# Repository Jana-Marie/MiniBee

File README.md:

# MiniBee

STM32WB5 based Zigbee (and other RF protocols) to adressable LED (e.g. WS2812, SK6812) bridge with a footprint of just 22*23.5mm and USB.

<table>
  <tbody>
    <tr>
      <td>
        
      </td>
      <td>
        
      </td>
    </tr>
    <tr>
      <td colspan="2">
        
      </td>
    </tr>
  </tbody>
</table>

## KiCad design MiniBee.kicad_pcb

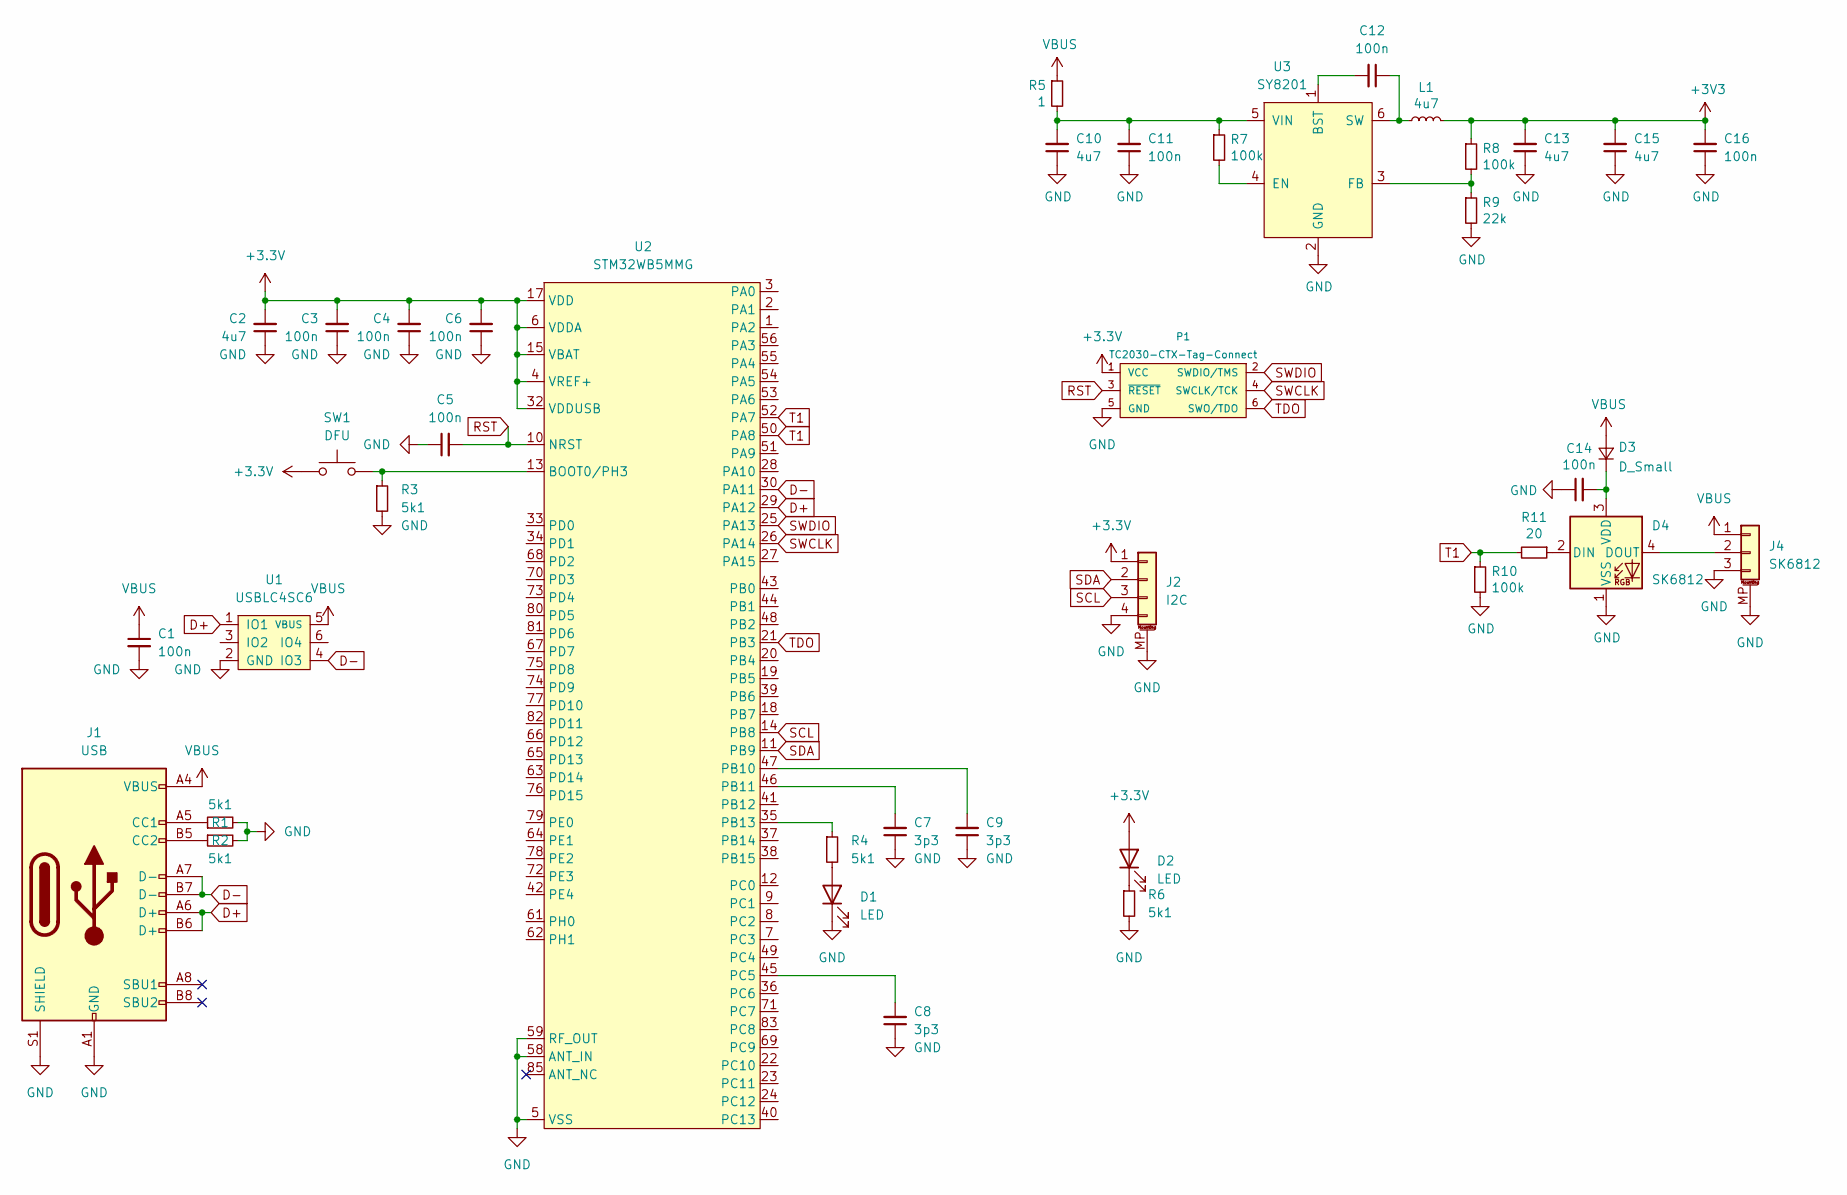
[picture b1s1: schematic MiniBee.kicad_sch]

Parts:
C1, C3, C4, C5, C6, C11, C12, C14, C16: 100n; C_0402
C2, C10, C13, C15: 4u7; C_0805
C7, C8, C9: 3p3; C_0402
D1, D2: LED; LED_0603_1608Metric
D3: D_Small; D_SOD-123F
D4: SK6812; LED_SK6812_PLCC4_5.0x5.0mm_P3.2mm
J1: USB; USB-C 16Pin
J2: I2C; Molex_PicoBlade_53398-0471_1x04-1MP_P1.25mm_Vertical
J4: SK6812; Molex_PicoBlade_53261-0371_1x03-1MP_P1.25mm_Horizontal
L1: 4u7; L_1210_3225Metric; LCSC C86070
P1: TC2030-CTX-Tag-Connect; TC2030
R1, R2, R3, R4, R6: 5k1; R_0402
R5: 1; R_0603
R7, R8, R10: 100k; R_0402
R9: 22k; R_0402
R11: 20; R_0402
SW1: DFU; SW_SPST_EVQP7C
U1: USBLC4SC6; SOT-23-6
U2: STM32WB5MMG
U3: SY8201; SOT-23-6

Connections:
D+: J1.A6 (D+), J1.B6 (D+), U1.1 (IO1), U2.29 (PA12)
D-: J1.A7 (D-), J1.B7 (D-), U1.4 (IO3), U2.30 (PA11)
GND: C1.2, C2.1, C3.1, C4.1, C5.1, C6.1, C7.1, C8.1, C9.1, C10.1, C11.1, C13.1, C14.1, C15.1, C16.1, D1.1 (K), D4.1 (VSS), J1.A1 (GND), J1.A12 (GND), J1.B1 (GND), J1.B12 (GND), J1.S1 (SHIELD), J2.4, J2.MP (MountPin), J4.3, J4.MP (MountPin), P1.5 (GND), R1.2, R2.2, R3.2, R6.2, R9.2, R10.2, U1.2 (GND), U2.5 (VSS), U2.16 (VSS), U2.31 (VSS), U2.57 (VSS), U2.58 (ANT_IN), U2.59 (RF_OUT), U2.60 (VSS), U2.84 (VSS), U2.86 (VSS), U3.2 (GND)
unnamed: C7.2, U2.46 (PB11)
unnamed: C8.2, U2.45 (PC5)
unnamed: C9.2, U2.47 (PB10)
unnamed: C10.2, C11.2, R5.2, R7.1, U3.5 (VIN)
unnamed: C12.1, L1.1, U3.6 (SW)
unnamed: C12.2, U3.1 (BST)
unnamed: C14.2, D3.1 (K), D4.3 (VDD)
unnamed: D1.2 (A), R4.2
unnamed: D2.1 (K), R6.1
unnamed: D4.2 (DIN), R11.1
unnamed: D4.4 (DOUT), J4.2
unnamed: J1.A5 (CC1), R1.1
unnamed: J1.B5 (CC2), R2.1
unnamed: R3.1, SW1.2, U2.13 (BOOT0/PH3)
unnamed: R4.1, U2.35 (PB13)
unnamed: R7.2, U3.4 (EN)
unnamed: R8.2, R9.1, U3.3 (FB)
RST: C5.2, P1.3 (~RESET), U2.10 (NRST)
SCL: J2.3, U2.14 (PB8)
SDA: J2.2, U2.11 (PB9)
SWCLK: P1.4 (SWCLK/TCK), U2.26 (PA14)
SWDIO: P1.2 (SWDIO/TMS), U2.25 (PA13)
T1: R10.1, R11.2, U2.50 (PA8), U2.52 (PA7)
TDO: P1.6 (SWO/TDO), U2.21 (PB3)
VBUS: C1.1, D3.2 (A), J1.A4 (VBUS), J1.A9 (VBUS), J1.B4 (VBUS), J1.B9 (VBUS), J4.1, R5.1, U1.5 (VBUS)

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
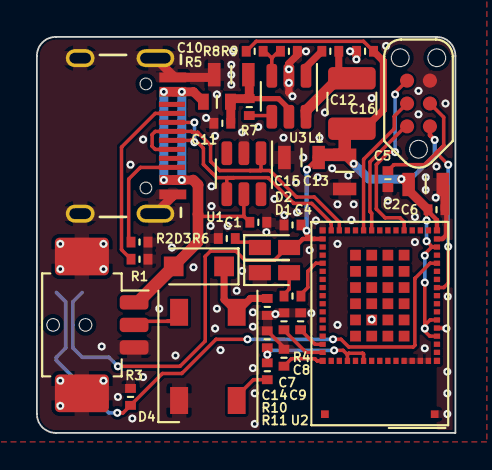
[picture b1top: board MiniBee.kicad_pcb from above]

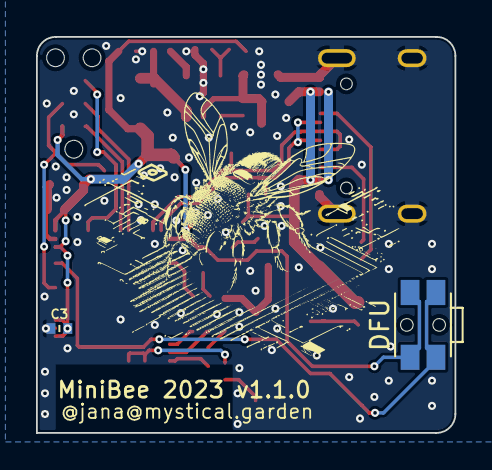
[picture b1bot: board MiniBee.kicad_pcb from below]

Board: 2 copper layers, 23.2 x 22.0 mm, 39 parts (2 on the bottom side), 27 nets.

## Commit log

2023-01-03 updated gitignore
2023-01-03 added kicad files
2023-03-02 added more images
2023-03-02 updated project files
